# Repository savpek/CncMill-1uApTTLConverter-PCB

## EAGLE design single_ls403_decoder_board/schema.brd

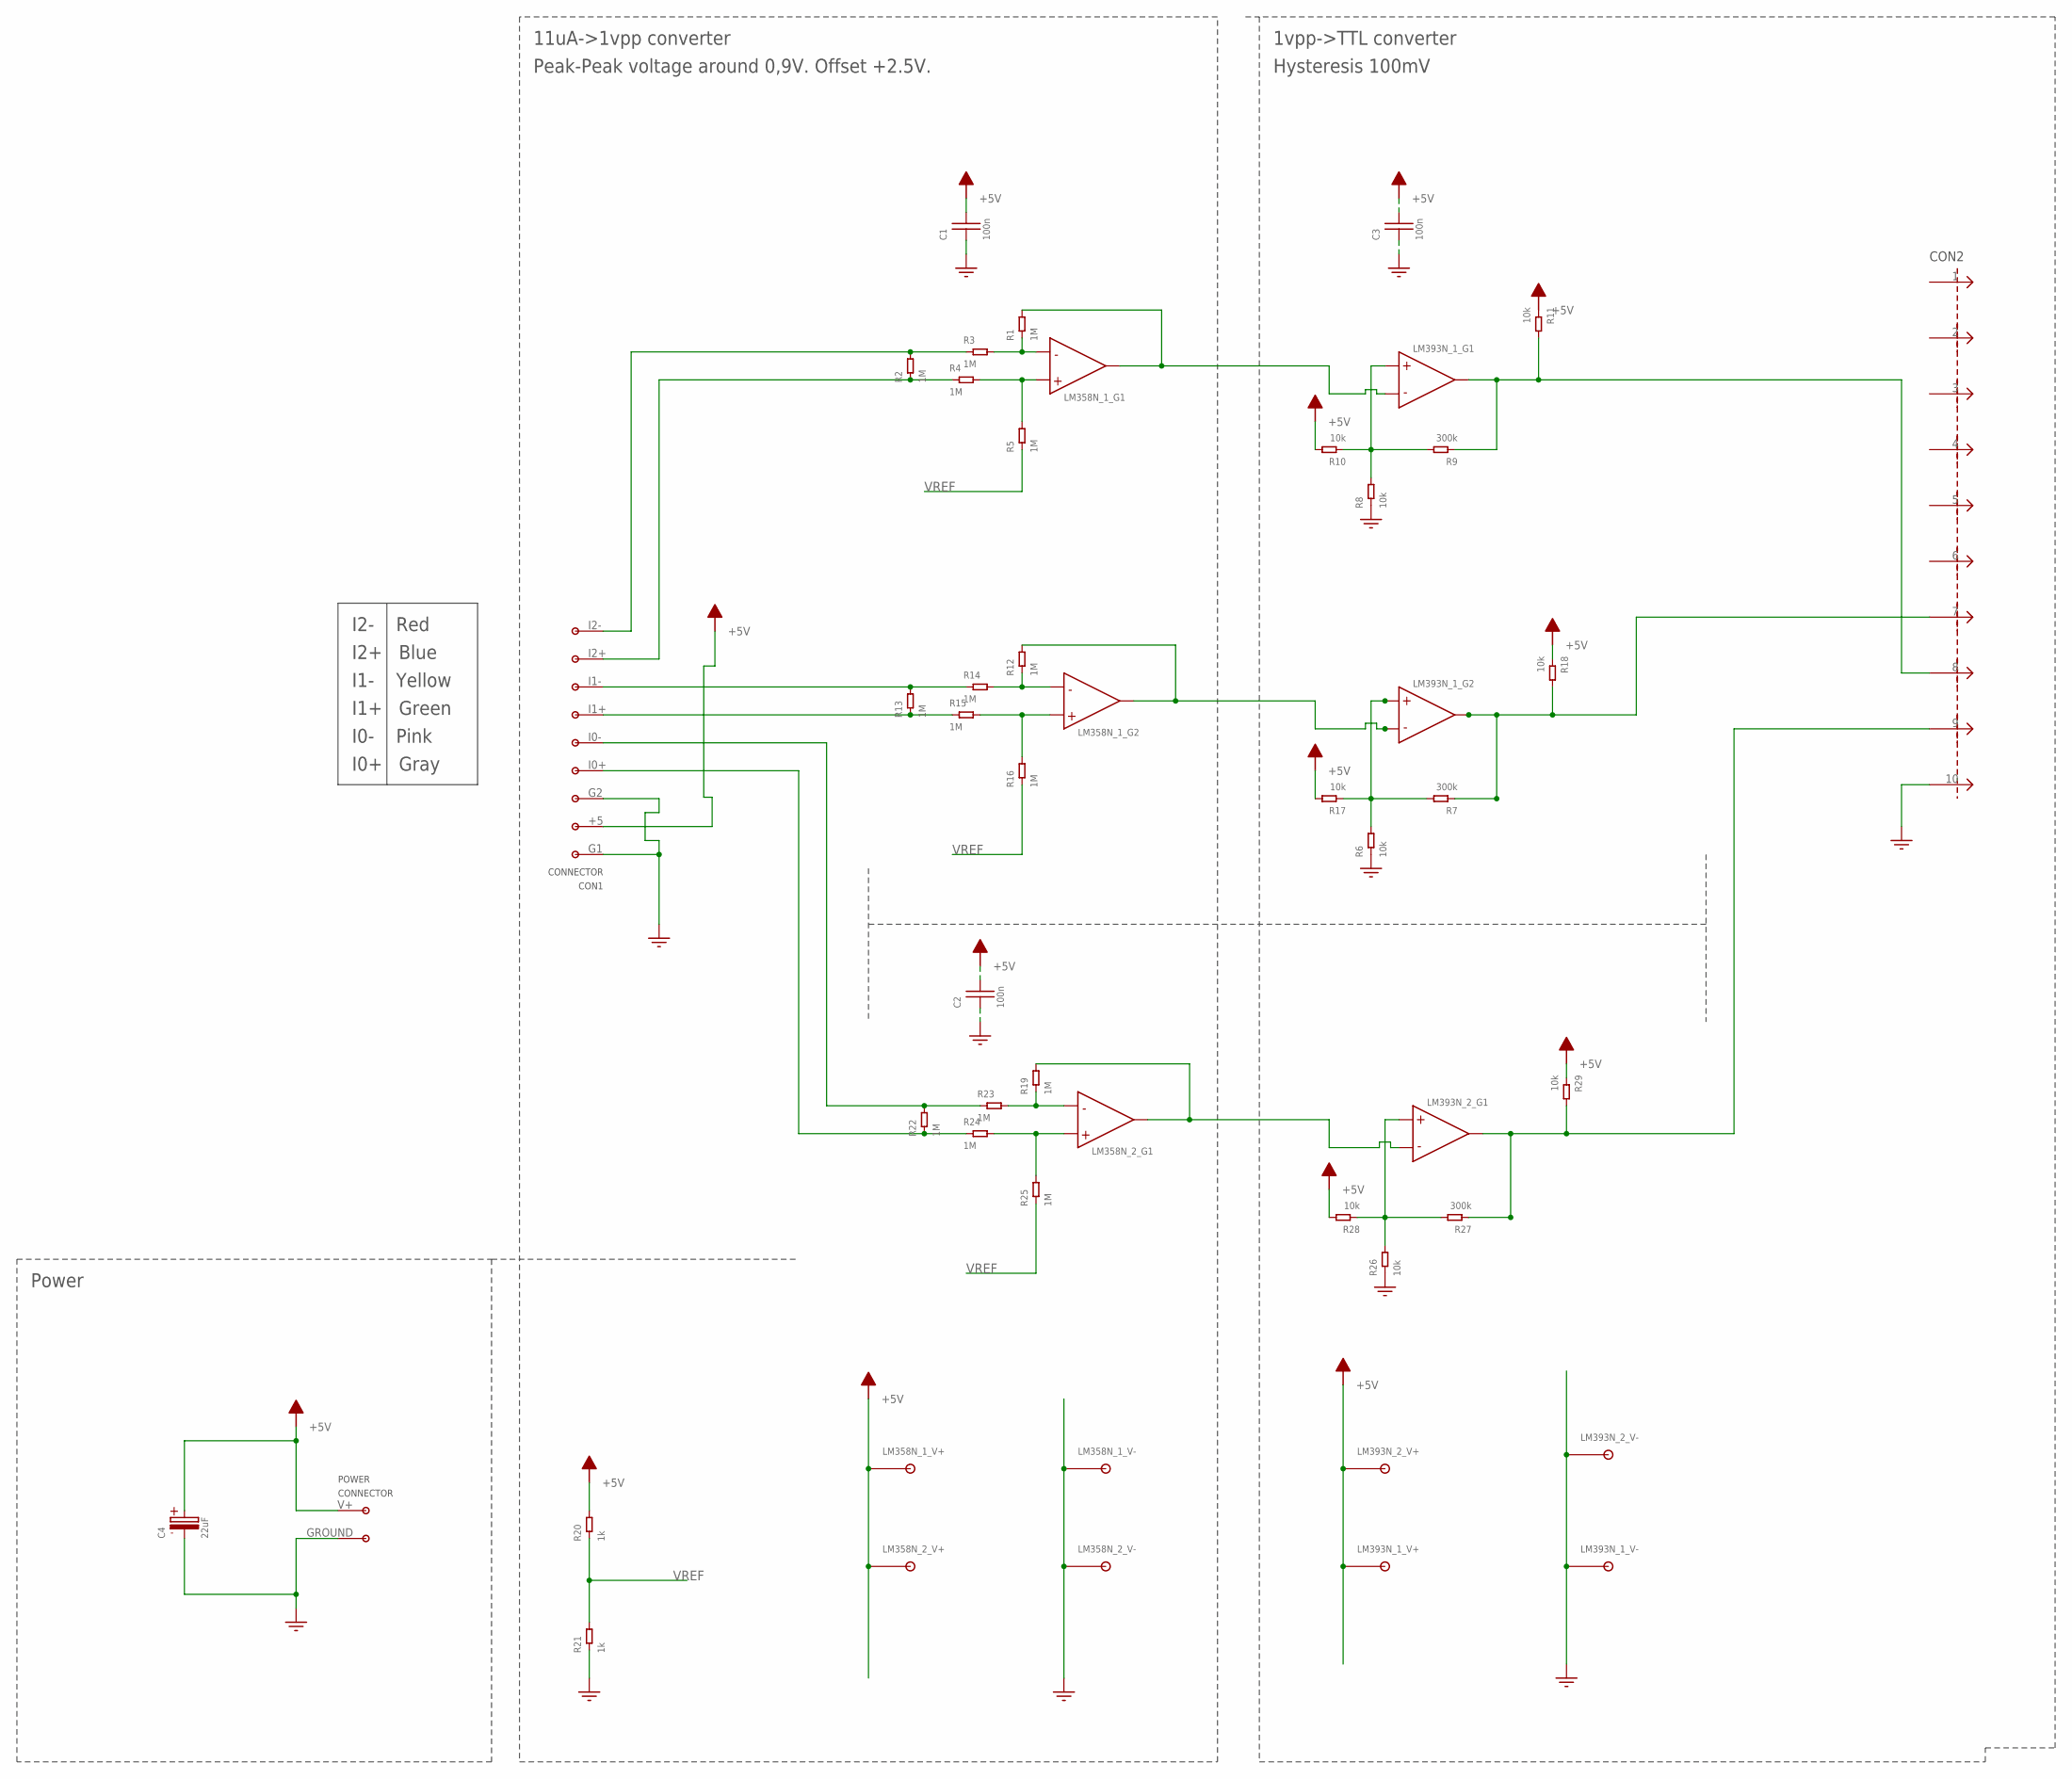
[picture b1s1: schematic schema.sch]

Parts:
C1, C2, C3: 100n; R0805
C4: 22uF; E2,5-6
CON1: LS403_INPUT_CONNECTOR
CON2: CONNECTOR_10PINGENERIC2X5; 2X5_GENERIC
LM358N_1, LM358N_2: LM358DIL8; DIL08
LM393N_1, LM393N_2: LM393N; DIL08
POWER: 2_PIN_CONNECTOR; 2_PIN_GENERIC_POWER_CONNECTOR
R1, R2, R3, R4, R5, R12, R13, R14, R15, R16, R19, R22, R23, R24, R25: 1M; R0805
R6, R8, R10, R11, R17, R18, R26, R28, R29: 10k; R0805
R7, R9, R27: 300k; R0805
R20, R21: 1k; R0805

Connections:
+5V: C1.1, C2.1, C3.1, C4.+, CON1.+5, LM358N_1.8 (SUPPLYPIN), LM358N_2.8 (SUPPLYPIN), LM393N_1.8 (SUPPLYPIN), LM393N_2.8 (SUPPLYPIN), POWER.V+, R10.2, R11.1, R17.2, R18.1, R20.2, R28.2, R29.1
GND: C1.2, C2.2, C3.2, C4.-, CON1.G1, CON1.G2, CON2.10, LM358N_1.4 (SUPPLYPIN), LM358N_2.4 (SUPPLYPIN), LM393N_1.4 (SUPPLYPIN), LM393N_2.4 (SUPPLYPIN), POWER.GROUND, R6.1, R8.1, R21.1, R26.1
I0_OUT: CON2.9, LM393N_2.1 (OUT), R27.1, R29.2
I1_OUT: CON2.7, LM393N_1.7 (OUT), R7.1, R18.2
I2_OUT: CON2.8, LM393N_1.1 (OUT), R9.1, R11.2
unnamed: LM393N_1.5 (+), R6.2, R7.2, R17.1
unnamed: LM358N_1.2 (-), R1.1, R3.2
unnamed: LM358N_1.1 (OUT), LM393N_1.2 (-), R1.2
unnamed: CON1.I2-, R2.2, R3.1
unnamed: CON1.I2+, R2.1, R4.1
unnamed: LM358N_1.3 (+), R4.2, R5.2
unnamed: LM393N_1.3 (+), R8.2, R9.2, R10.1
unnamed: LM358N_1.6 (-), R12.1, R14.2
unnamed: LM358N_1.7 (OUT), LM393N_1.6 (-), R12.2
unnamed: CON1.I1-, R13.2, R14.1
unnamed: CON1.I1+, R13.1, R15.1
unnamed: LM358N_1.5 (+), R15.2, R16.2
unnamed: LM358N_2.2 (-), R19.1, R23.2
unnamed: LM358N_2.1 (OUT), LM393N_2.2 (-), R19.2
unnamed: CON1.I0-, R22.2, R23.1
unnamed: CON1.I0+, R22.1, R24.1
unnamed: LM358N_2.3 (+), R24.2, R25.2
unnamed: LM393N_2.3 (+), R26.2, R27.2, R28.1
VREF: R5.1, R16.1, R20.1, R21.2, R25.1

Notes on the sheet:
11uA->1vpp converter
1vpp->TTL converter
Peak-Peak voltage around 0,9V. Offset +2.5V.
Hysteresis 100mV
I1+ Green
I1- Yellow
I2+ Blue
I2- Red
I0- Pink
I0+ Gray
Power

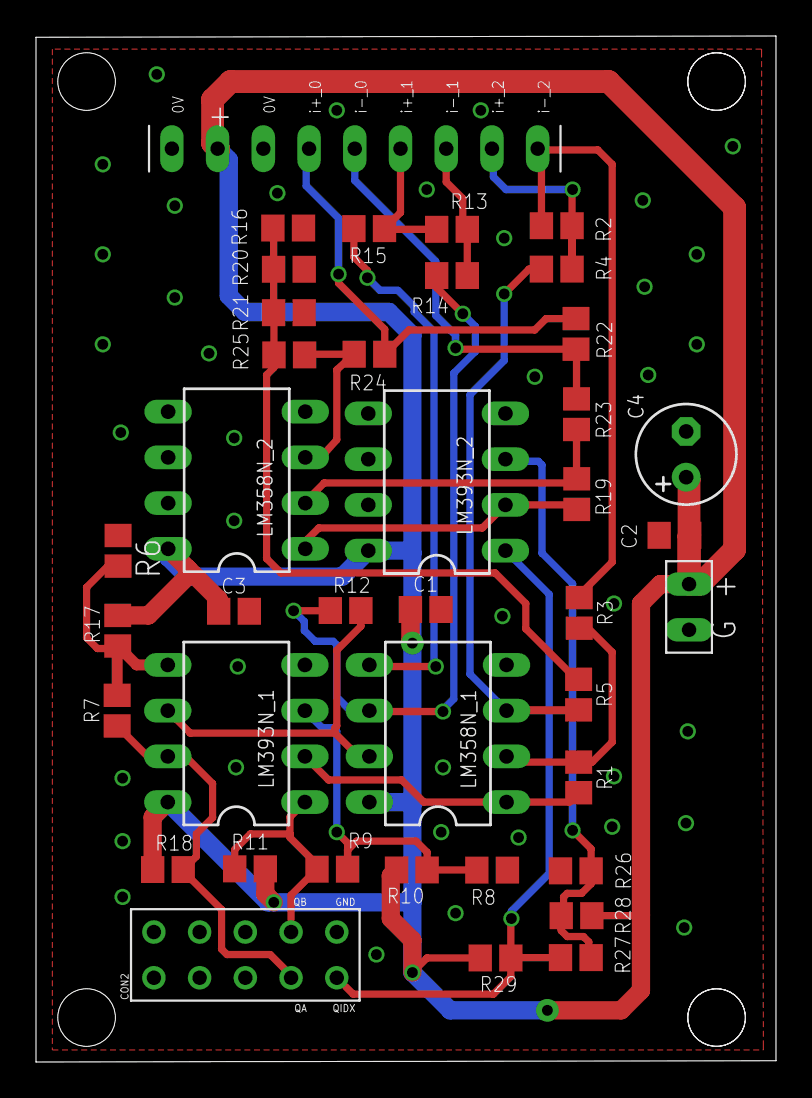
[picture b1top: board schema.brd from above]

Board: 2 copper layers, 41.1 x 57.0 mm, 40 parts (0 on the bottom side), 24 nets.

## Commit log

2012-07-25 Initial commit.
2012-10-20 Removed old test projects.
2012-10-20 Packages changed and parts placed on PCB
2012-10-20 New version of TTL converter ready for batch.
